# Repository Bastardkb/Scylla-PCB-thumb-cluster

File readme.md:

# Scylla PCB - thumbs

Flexible PCB made for the Scylla.

With per-key RGB.

This repository contains all files necessary to order a PCB.

If you want to modify the design files, the Kicad sources are included.
If you just want to order the PCBs, check out the Release section which contain the gerber files.

## How to order

Order with a 0.6mm or 0.8mm PCB thickness

## License

Licensed under CC BY-NC-SA 4.0
Copyright Quentin Lebastard 2021

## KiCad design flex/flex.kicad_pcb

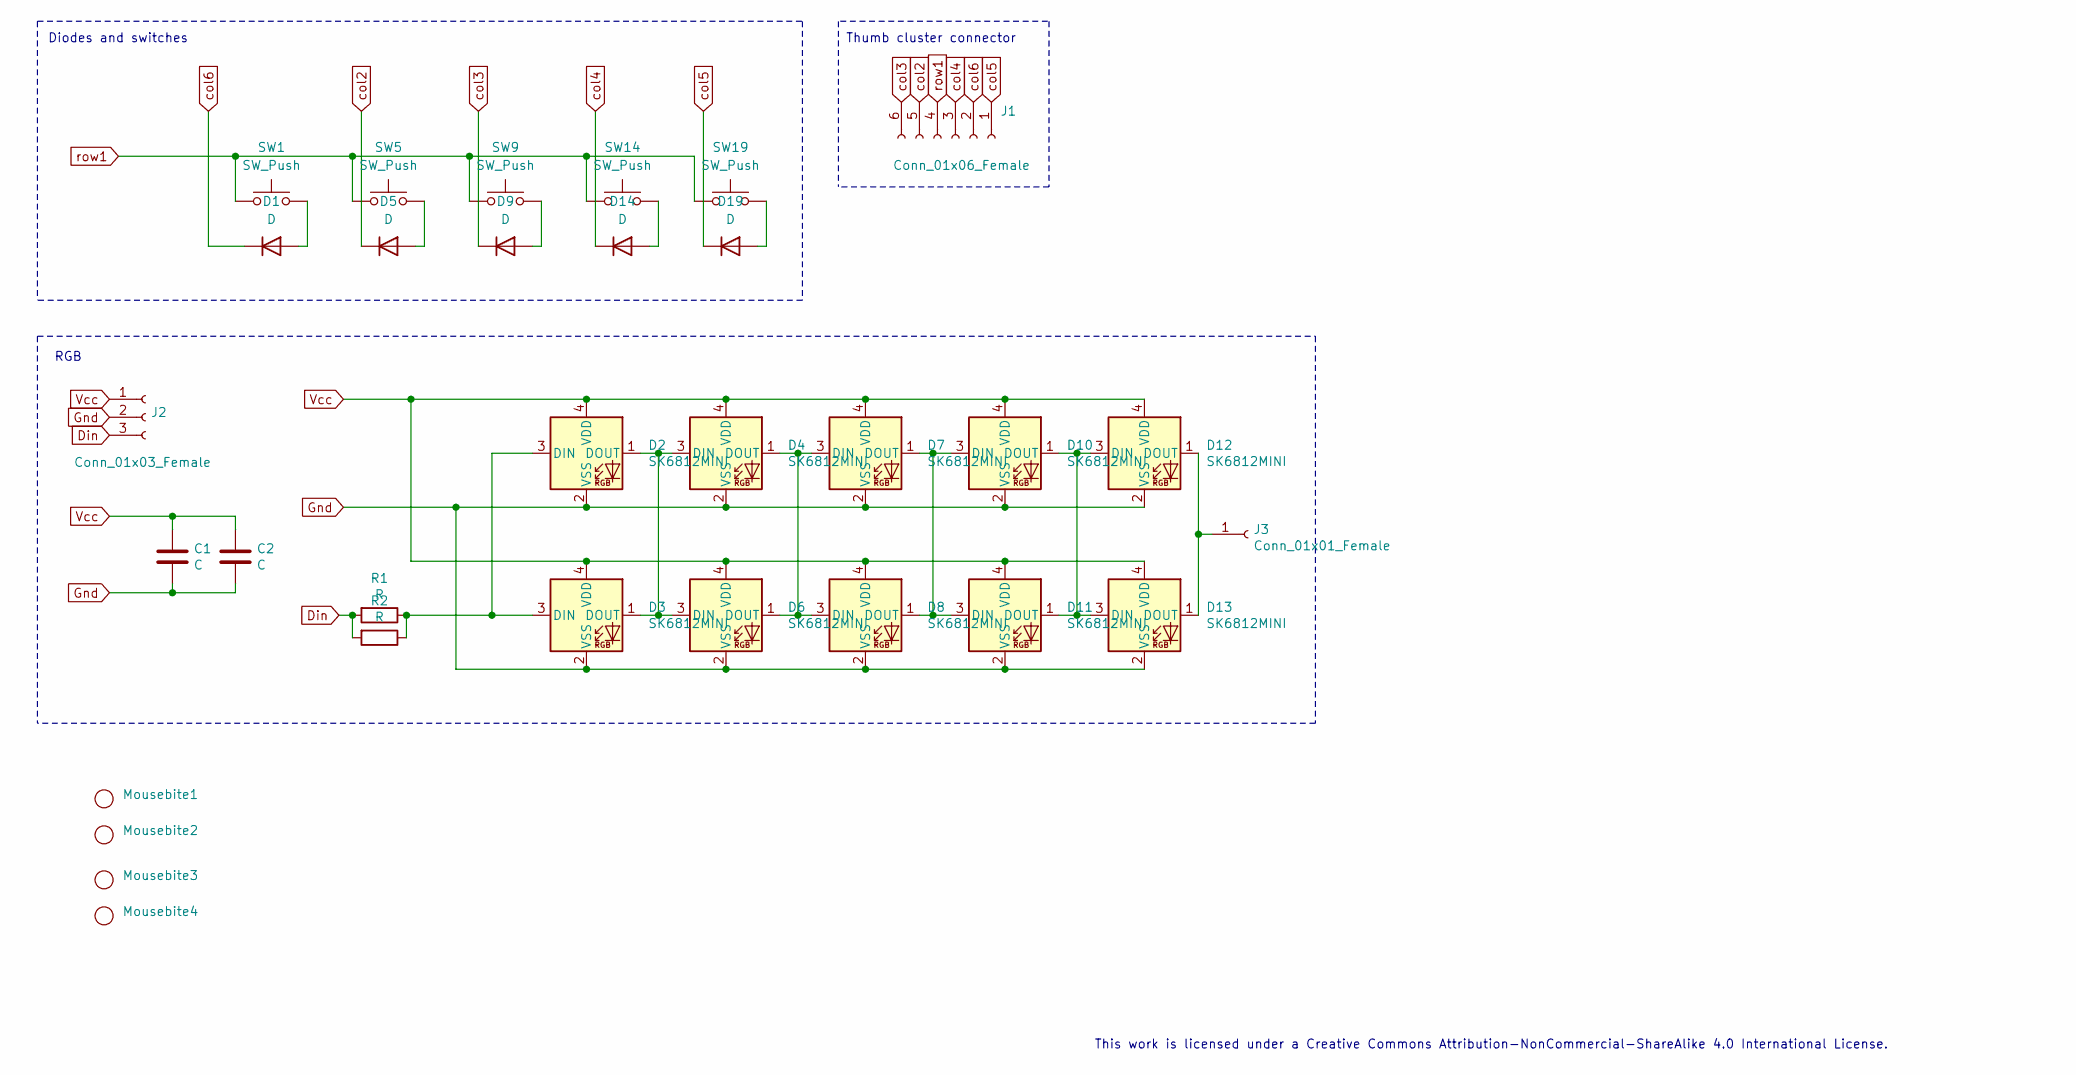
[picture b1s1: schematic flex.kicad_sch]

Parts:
C1, C2: C; LED_1206_3216Metric_Pad1.42x1.75mm_HandSolder
D1, D5, D9, D14, D19: D; Diode_TH_SOD123
D2, D4, D7, D10, D12: SK6812MINI; SK6812_mini_e_corners
D3, D6, D8, D11, D13: SK6812MINI; SK6812_mini_e_corners_noedgecuts
J1: Conn_01x06_Female; PinHeader_1x06_P2.54mm_Vertical
J2: Conn_01x03_Female; PinHeader_1x03_P2.54mm_Vertical
J3: Conn_01x01_Female; PinHeader_1x01_P2.54mm_Vertical
Mousebite1, Mousebite2, Mousebite3, Mousebite4: mousebite
R1, R2: R; R_1206_3216Metric_Pad1.42x1.75mm_HandSolder
SW1, SW5, SW9, SW14, SW19: SW_Push; SW_MX_reversible

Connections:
Din: J2.3, R1.2, R2.2
Gnd: C1.2, C2.2, D2.2 (VSS), D3.2 (VSS), D4.2 (VSS), D6.2 (VSS), D7.2 (VSS), D8.2 (VSS), D10.2 (VSS), D11.2 (VSS), D12.2 (VSS), D13.2 (VSS), J2.2
unnamed: D1.2 (A), SW1.2
unnamed: D2.3 (DIN), D3.3 (DIN), R1.1, R2.1
unnamed: D2.1 (DOUT), D3.1 (DOUT), D4.3 (DIN), D6.3 (DIN)
unnamed: D4.1 (DOUT), D6.1 (DOUT), D7.3 (DIN), D8.3 (DIN)
unnamed: D5.2 (A), SW5.2
unnamed: D9.2 (A), SW9.2
unnamed: D7.1 (DOUT), D8.1 (DOUT), D10.3 (DIN), D11.3 (DIN)
unnamed: D10.1 (DOUT), D11.1 (DOUT), D12.3 (DIN), D13.3 (DIN)
unnamed: D12.1 (DOUT), D13.1 (DOUT), J3.1
unnamed: D14.2 (A), SW14.2
unnamed: D19.2 (A), SW19.2
Vcc: C1.1, C2.1, D2.4 (VDD), D3.4 (VDD), D4.4 (VDD), D6.4 (VDD), D7.4 (VDD), D8.4 (VDD), D10.4 (VDD), D11.4 (VDD), D12.4 (VDD), D13.4 (VDD), J2.1
col2: D5.1 (K), J1.5
col3: D9.1 (K), J1.6
col4: D14.1 (K), J1.3
col5: D19.1 (K), J1.1
col6: D1.1 (K), J1.2
row1: J1.4, SW1.1, SW5.1, SW9.1, SW14.1, SW19.1

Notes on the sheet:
Diodes and switches
RGB
Thumb cluster connector
This work is licensed under a Creative Commons Attribution-NonCommercial-ShareAlike 4.0 International License.

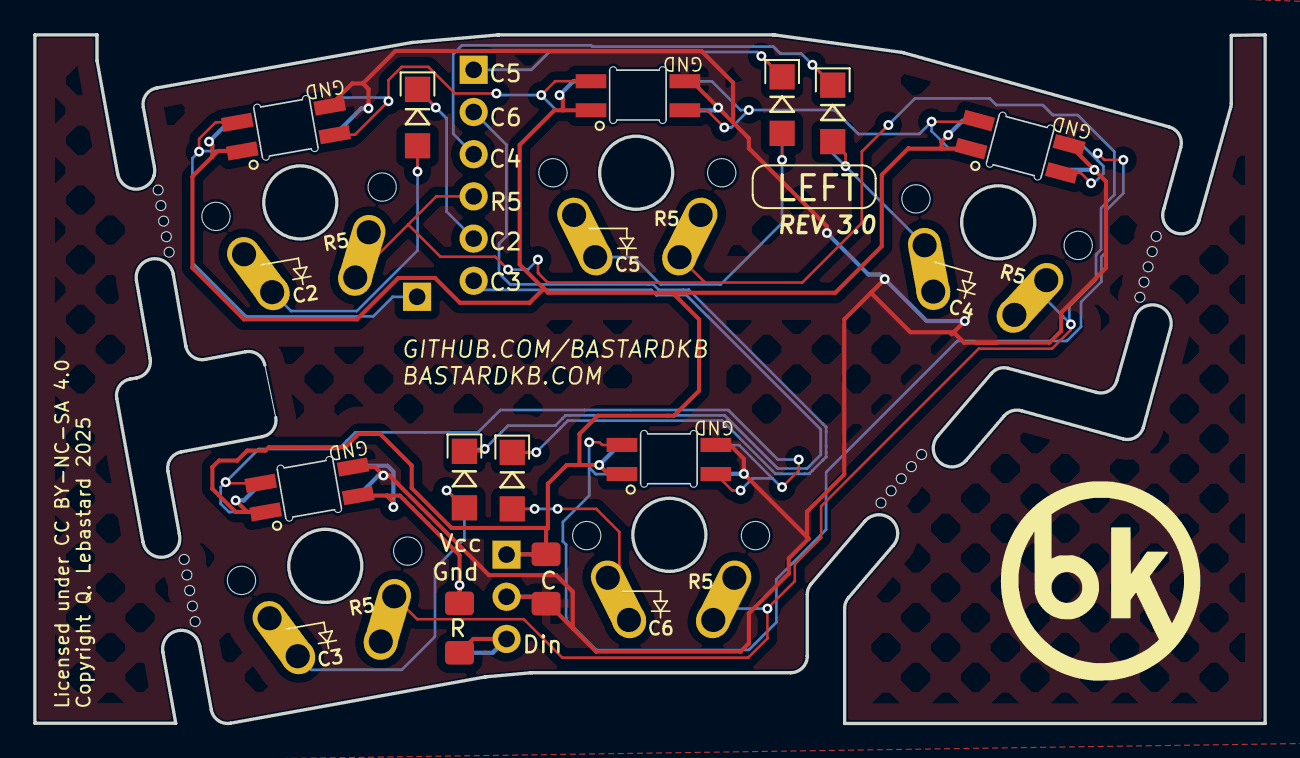
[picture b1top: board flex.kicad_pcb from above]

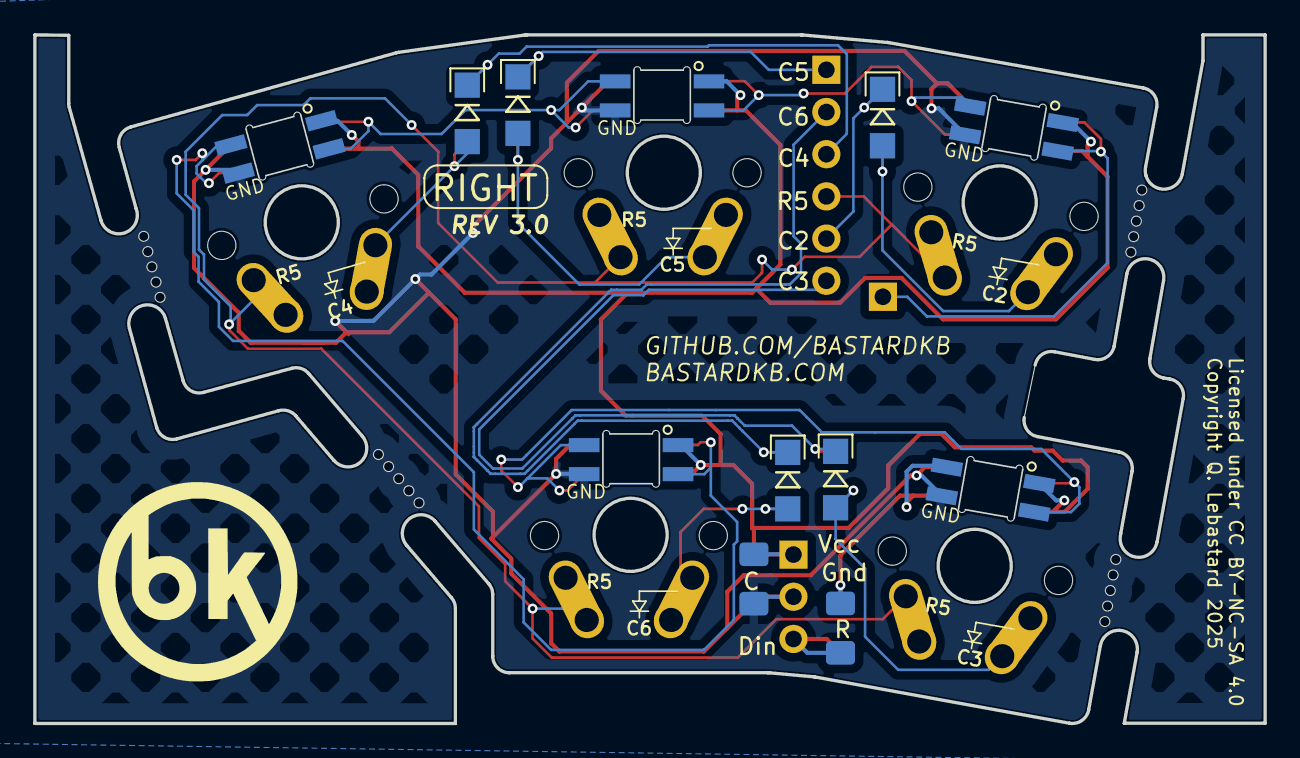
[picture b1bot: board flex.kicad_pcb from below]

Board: 2 copper layers, 74.1 x 41.5 mm, 31 parts (7 on the bottom side), 20 nets.

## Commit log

2022-02-25 upload stuff
2022-02-25 licenses
2022-03-01 move rgb connector
2022-03-01 vcc gnd routing
2022-03-01 connect all signals per led
2022-03-01 connect led signals
2022-03-01 flip c6 and c5
2022-03-01 silkscreen
2022-03-01 move r away from connector
2025-04-10 mouse bites
2025-04-10 mousebites
2025-04-10 update RGB
2025-04-10 routing serttings
2025-04-10 routing
2025-04-10 font
2025-04-11 edge cuts
2025-04-11 netclass rules

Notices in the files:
flex/flex.kicad_pcb:
Copyright Q. Lebastard 2025
flex/flex.kicad_sch:
Copyright Quentin Lebastard 2022
